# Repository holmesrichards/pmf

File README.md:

# Pole mixing filter

This is a multimode VCF in Kosmo format based on a [design](https://electricdruid.net/multimode-filters-part-2-pole-mixing-filters) by Electric Druid (ED). It uses pole mixing to achieve multiple filter behaviors.

## Design notes

### Changes from ED design

* 82k resistors (RF) changed to 100k; 91k resistors (RC) to fixed + trimmer.
* Added AC coupling capacitor on input signal to resonance compensation mixer.
* Added resistor on resonance input pin missing from original schematics. Changed its value from 51k to 120k.
* Added op amp buffers and pulldown resistors on LP1–4 after AC coupling capacitors.
* Added second inverting stage on input. Reduced first stage gain to 0.51 and increased output stage gain by the same factor.
* Changed ordering of 1st to 6th mixes.
* In 4P HP mix, changed 4.99k resistor to sum of 2k and 3k.
* Changed BP resistors for unity gain at peak.
* Changed 7th mix to {1, 2, 2, 0, 0} notch.
* Original had incorrect resistances for 8th mix; fixed.
* 7th and 8th mix have enough resistor footprints to implement any desired mix.
* Multiplexer replaced with rotary switch.
* Added header for expansion.

### Discussion

As discussed [here](Docs/tolerances.md), it is important that filter stages have unity DC gain and mixer ratios be correct at a level of about 1% or better, preferably more like 0.1% for the mixer resistors.

The 82k feedback resistors used in the ED design are a puzzle: Per the CEM3320 datasheet, they result in a gain of around 0.82. In the datasheet circuit these resistors are 100k giving gain 0.999. On the breadboard I found some gain variation (even if I matched the resistors), so I replaced the 91k resistors (RI, RC) with fixed + trimmer combinations.

If there is a DC offset on the input signal (if for instance it goes 0 to 5 V), then, due to its being DC coupled to the resonance compensation mixer, turning up the resonance CV would drive the DC offset of the output signal higher. Even with a 0 to 2 V input, the output could exceed 9 V due to the large offset. This is too large: With Vcc = 12 V, maximum output before clipping is about 9 V. Adding a capacitor to AC couple the input signal to the compensation mixer eliminates this problem.

The ED schematics omit a resistor on the resonance input pin. In the comments Tom Wiltshire says this should be 51k. I found this value would cause self oscillation to start up at a very low position of the resonance knob, so changed it to 120k.

With an input of 5 V (or -5 V) or above, the filter stage outputs would try to go to or above about 10 V. I reduced the input gain by a factor of 0.51 to keep below that limit. ±5 V is the standard audio signal range in my synth. Of course if you use two summed inputs they might exceed 5 V, so some additional attenuation may be needed. I also added a second inverting stage with the thought of preserving the phase going into the filter. However there is an inverting stage at the output, so it probably would have been better to leave this second stage out. Not quite sure what I was thinking!

ED's mixers have been re-ordered, just because I felt 2 pole should go before 4 pole. The E96 4.99k resistor has been replaced by E24 2k and 3k in series, because who want to order one resistor from DigiKey that Tayda doesn't carry? The resistor values used by ED in the BP mixers result in peak amplitudes 6 or 12 dB below the input level; I reduced them to get unity gain at the peaks. I wasn't that enthusiastic about the seventh filter — a rather weird combination of things giving rise to a sort of band pass plus notch response — so I replaced it with a second (sharper, deadlier) notch filter.

I didn't see much point in messing around with a multiplexer chip. I used a rotary switch instead. If you really want electronically selectable filter shapes, see the Expansion section below.

The mixers that are not selected by the rotary switch had floating outputs and corrupted the LP1–LP4 signals until I added op amp buffers after the AC coupling capacitors. I believe the same problem would occur with a multiplexer. To avoid bias current charging of the capacitors, I also added 1M resistors to ground between the capacitors and the op amps.

### Choose your own

To accommodate other builders with other preferences (or future me with other preferences), in the last two filters enough resistor (or jumper) footprints have been provided to build almost any mixer allowing whatever filter responses you want. Each of the LP1, LP2, LP3, and LP4 signals has two footprints in series. For example, to re-create ED's seventh filter, [0, 1, 3, 6, 4]: Omit the R<sub>IN</sub> resistor, use 30k and a wire jumper for the two R<sub>LP1</sub> resistors, 10k+jumper for R<sub>LP2</sub>, 2k+3K for R<sub>LP3</sub>, and 7.5k+jumper for R<sub>LP4</sub>. To build the filters shown in the schematic, follow the silkscreen: Use wire jumpers for the jumper footprints and leave the DNF footprints empty.

A catalog of 40+ filters is in [Docs/catalog.md](Docs/catalog.md).

### Expansion

There is an expansion header on the PCB. This could be used to mount a daughterboard giving more mixes. Or it could be used for a ribbon cable connection to an expansion module, which could e.g. provide user-changeable mixes (5 rotary switches?) or a microcontroller-based variable mixer, potentially even with CV input to switch mixes. This repo includes a design for a daughterboard providing four additional builder-defined mixes. As with filters 7 and 8 on the main module, there are two footprints for each of the LP1, LP2, LP3, and LP4 signals and you can populate both with resistors, use one resistor and one jumper, or omit both to get the mixes you desire. This daughterboard has not been built or tested yet.

### Filters

The filters are as follows. Numbers indicate coefficients for input, -LP1, LP2, -LP3, and LP4 mixing.

* 0, 0, 1, 0, 0 — 2 pole low pass
* 0, 0, 0, 0, 1 — 4 pole low pass
* 1, 2, 1, 0, 0 — 2 pole high pass
* 1, 4, 6, 4, 1 — 4 pole high pass
* 0, 2, 2, 0, 0 — 2 pole band pass
* 0, 0, 4, 8, 4 — 4 pole band pass
* 1, 2, 2, 0, 0 — Notch A
* 1, 2, 2, 2, 2 — Notch B

Here are Bode plots for these filters:

### Cancellation and tolerances

See discussion [here](Docs/tolerances.md).

## Software

The plots above were produced with a Python script included in this repo's Software folder. For a usage example see plots.sh in that folder. Libraries matplotlib, numpy, sys, and re are required. 

For the formulas for pole mixing upon which these plots are based, see [https://expeditionelectronics.com/Diy/Polemixing/math](https://expeditionelectronics.com/Diy/Polemixing/math). I believe there are some errors: the formulas for the imaginary parts of the numerator and denominator should have the opposite sign.

## Current draw
? mA +12 V, ? mA -12 V

## Photos

## Documentation

* [Schematic](Docs/pmf_schematic.pdf)
* PCB layout: [front of board 1](Docs/Layout/pmf_B1/pmf_B1_front.svg), [back of board 1](Docs/Layout/pmf_B1/pmf_B1_back.svg), [front of board 2](Docs/Layout/pmf_B2/pmf_B2_front.svg), [back of board 2](Docs/Layout/pmf_B2/pmf_B2_back.svg)
* [BOM](Docs/BOM/pmf_bom.md)
* [Daughterboard schematic](Docs/pmf_daughter_schematic.pdf)
* Daughterboard PCB layout: [front](Docs/Layout/pmf_daughter/pmf_daughter_front.svg), [back](Docs/Layout/pmf_daughter/pmf_daughter_back.svg)
* [Daughterboard BOM](Docs/BOM/pmf_daughter_bom.md)
* [Blog post](https://analogoutputblog.wordpress.com/2023/05/04/pole-mixing-filter/)

## GitHub repository

* [https://github.com/holmesrichards/pmf](https://github.com/holmesrichards/pmf)

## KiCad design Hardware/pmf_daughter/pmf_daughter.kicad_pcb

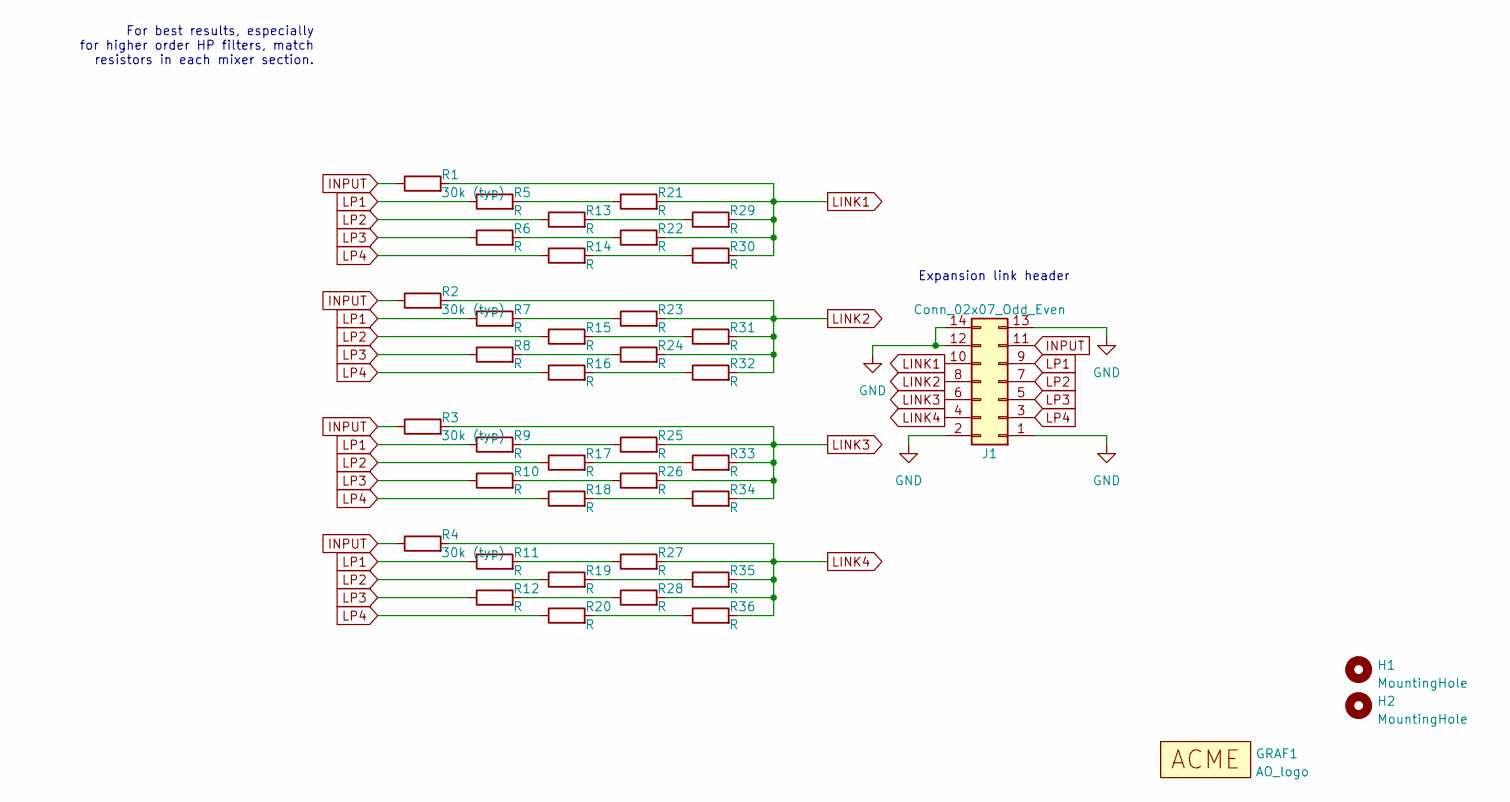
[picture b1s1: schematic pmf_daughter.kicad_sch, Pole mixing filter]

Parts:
GRAF1: AO_logo; analogoutput_12mm
H1, H2: MountingHole; MountingHole_3.2mm_M3
J1: Conn_02x07_Odd_Even; PinSocket_2x07_P2.54mm_Vertical
R1, R2, R3, R4: 30k (typ); R_Axial_DIN0207_L6.3mm_D2.5mm_P10.16mm_Horizontal
R5, R6, R7, R8, R9, R10, R11, R12, R13, R14, R15, R16, R17, R18, R19, R20, R21, R22, R23, R24, R25, R26, R27, R28, R29, R30, R31, R32, R33, R34, R35, R36: R; R_Axial_DIN0207_L6.3mm_D2.5mm_P10.16mm_Horizontal

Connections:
GND: J1.1, J1.2, J1.12, J1.13, J1.14
INPUT: J1.11, R1.1, R2.1, R3.1, R4.1
LINK1: J1.10, R1.2, R21.2, R22.2, R29.2, R30.2
LINK2: J1.8, R2.2, R23.2, R24.2, R31.2, R32.2
LINK3: J1.6, R3.2, R25.2, R26.2, R33.2, R34.2
LINK4: J1.4, R4.2, R27.2, R28.2, R35.2, R36.2
LP1: J1.9, R5.1, R7.1, R9.1, R11.1
LP2: J1.7, R13.1, R15.1, R17.1, R19.1
LP3: J1.5, R6.1, R8.1, R10.1, R12.1
LP4: J1.3, R14.1, R16.1, R18.1, R20.1
unnamed: R10.2, R26.1
unnamed: R11.2, R27.1
unnamed: R12.2, R28.1
unnamed: R13.2, R29.1
unnamed: R14.2, R30.1
unnamed: R15.2, R31.1
unnamed: R16.2, R32.1
unnamed: R17.2, R33.1
unnamed: R18.2, R34.1
unnamed: R19.2, R35.1
unnamed: R20.2, R36.1
unnamed: R5.2, R21.1
unnamed: R6.2, R22.1
unnamed: R7.2, R23.1
unnamed: R8.2, R24.1
unnamed: R9.2, R25.1

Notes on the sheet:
Expansion link header
For best results, especially for higher order HP filters, match resistors in each mixer section.

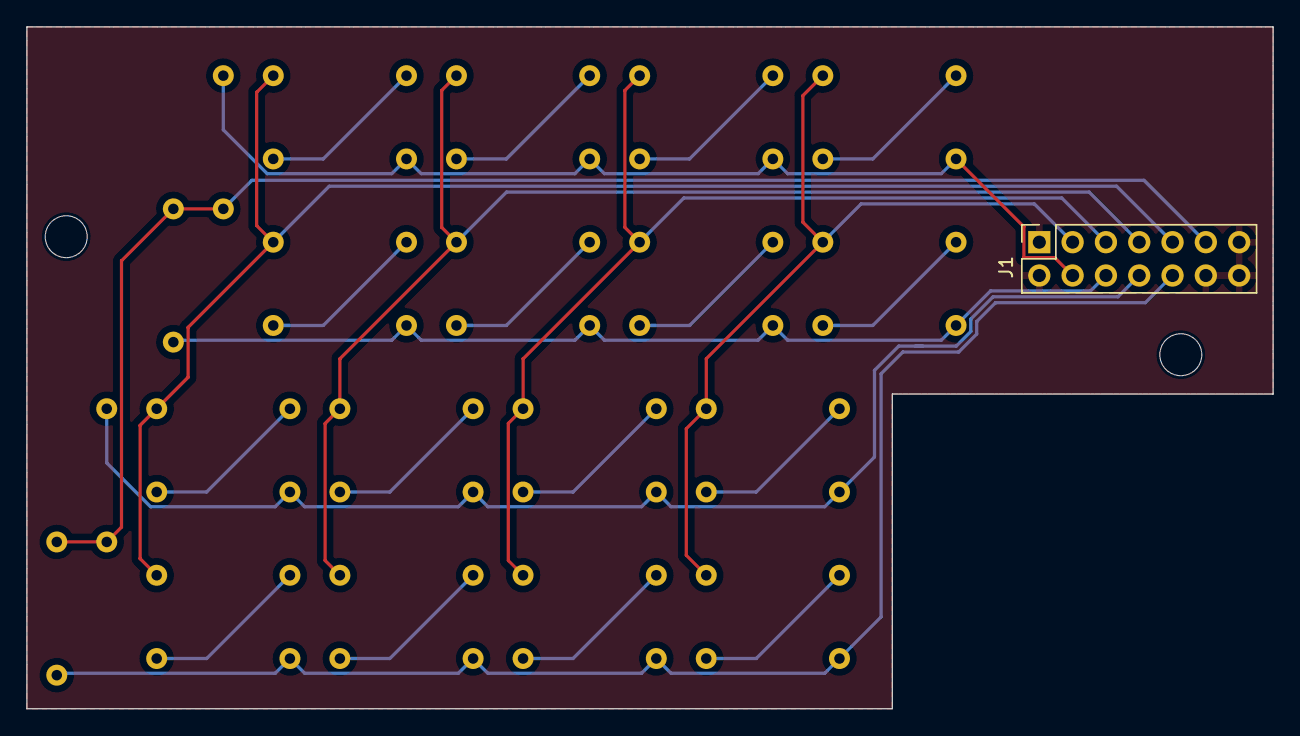
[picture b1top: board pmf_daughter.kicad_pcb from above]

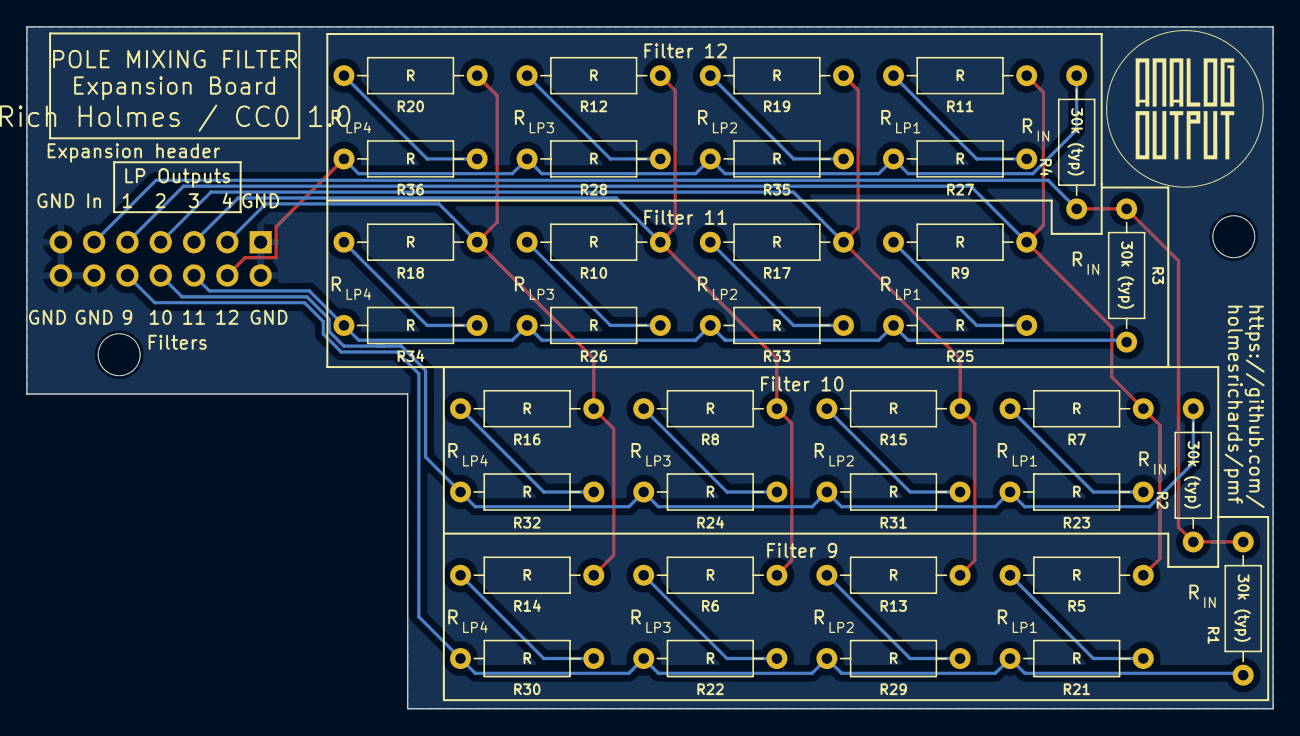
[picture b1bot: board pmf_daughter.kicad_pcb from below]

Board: 2 copper layers, 95.0 x 52.0 mm, 40 parts (37 on the bottom side), 26 nets.

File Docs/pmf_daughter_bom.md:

# pmf_daughter.kicad_sch BOM

Mon 16 Jan 2023 01:00:04 PM EST

Generated from schematic by Eeschema 7.0.0-rc1-unknown-00d77f624a~164~ubuntu22.04.1

**Component Count:** 37

| Refs | Qty | Component | Description | Vendor |
| ----- | --- | ---- | ----------- | ---- |
| J1 | 1 | Conn_02x07_Odd_Even | Generic connector, double row, 02x07, odd/even pin numbering scheme (row 1 odd numbers, row 2 even numbers), script generated (kicad-library-utils/schlib/autogen/connector/) |  |
| R1, R2, R3, R4 | 4 | 30k (typ) | Resistor | Tayda |
| R5, R6, R7, R8, R9, R10, R11, R12, R13, R14, R15, R16, R17, R18, R19, R20, R21, R22, R23, R24, R25, R26, R27, R28, R29, R30, R31, R32, R33, R34, R35, R36 | 32 | R | Resistor | Tayda |

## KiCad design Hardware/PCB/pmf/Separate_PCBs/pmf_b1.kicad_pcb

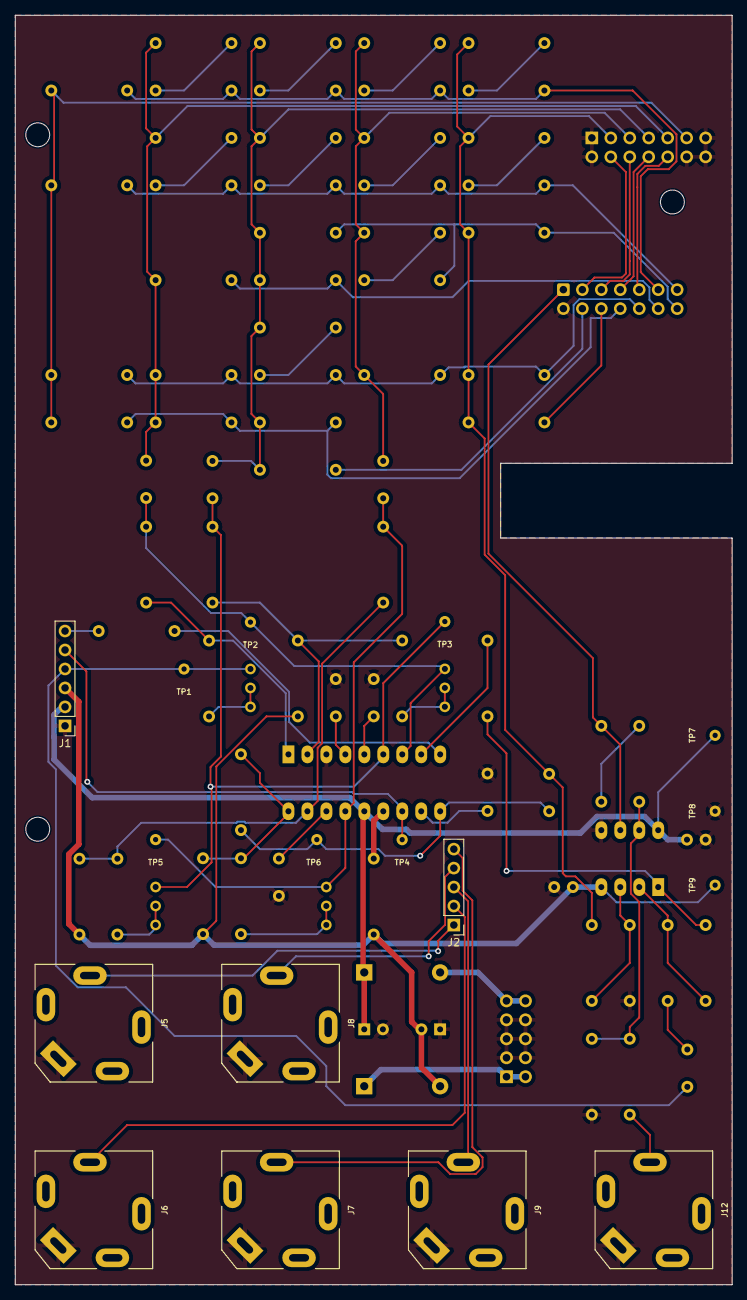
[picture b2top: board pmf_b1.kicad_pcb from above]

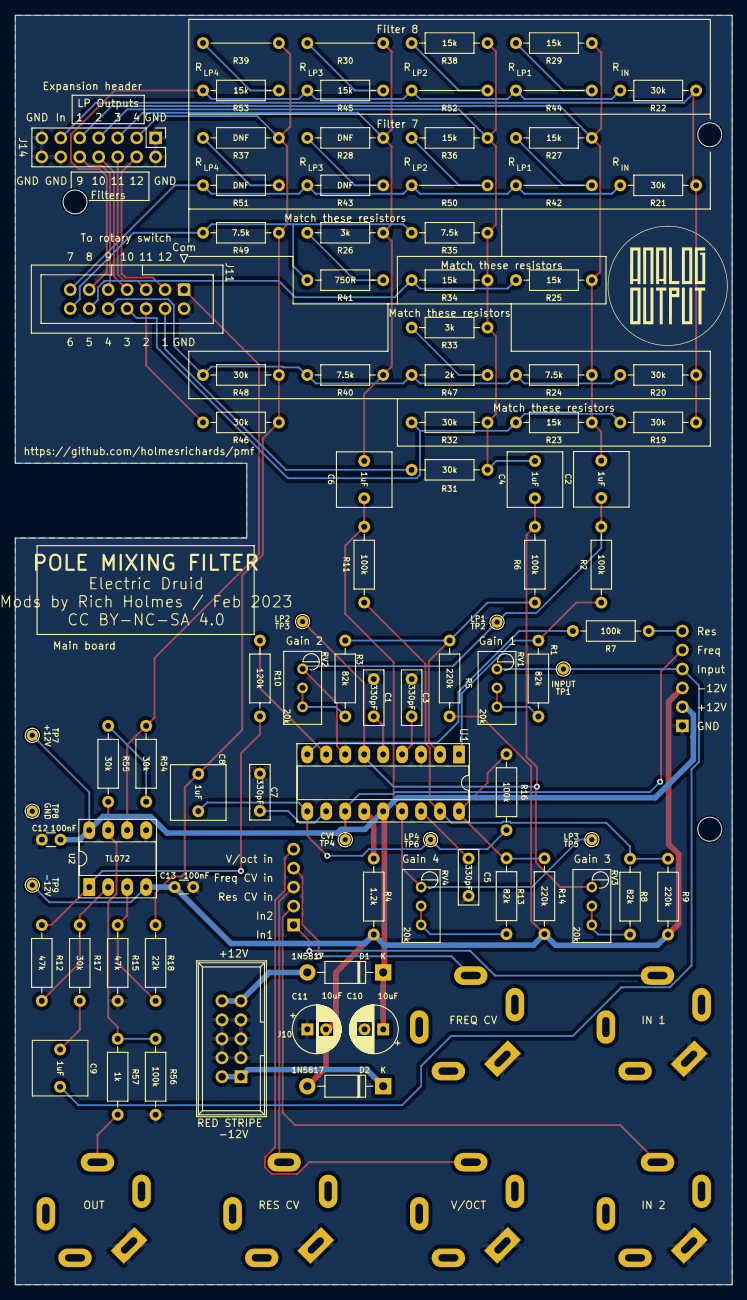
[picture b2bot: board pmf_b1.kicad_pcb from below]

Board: 2 copper layers, 96.0 x 170.0 mm, 104 parts (91 on the bottom side), 67 nets.

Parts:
B1: Board; Board_Marker
C1, C3, C5, C7: 330pF; C_Rect_L7.2mm_W2.5mm_P5.00mm_FKS2_FKP2_MKS2_MKP2
C2, C4, C6, C8, C9: 1uF; C_Rect_L7.2mm_W7.2mm_P5.00mm_FKS2_FKP2_MKS2_MKP2
C10, C11: 10uF; CP_Radial_D6.3mm_P2.50mm
C12, C13: 100nF; C_Disc_D3.0mm_W1.6mm_P2.50mm
D1, D2: 1N5817; D_DO-41_SOD81_P10.16mm_Horizontal
GRAF1: Holes; pmf_panel_holes
GRAF3: AO_logo; analogoutput
H1, H2, H3: MountingHole; MountingHole_3.2mm_M3
J1: Conn_01x06_Pin; PinHeader_1x06_P2.54mm_Vertical
J2: Conn_01x05_Pin; PinHeader_1x05_P2.54mm_Vertical
J5, J6, J7, J8, J9, J12: AudioJack2; Jack_6.35mm_PJ_629HAN_slots
J10: Synth_power_2x5; Power_Header
J11: Conn_02x07_Odd_Even; IDC-Header_2x07_P2.54mm_Vertical
J14: Conn_02x07_Odd_Even; PinHeader_2x07_P2.54mm_Vertical
R1, R3, R8, R13: 82k; R_Axial_DIN0207_L6.3mm_D2.5mm_P10.16mm_Horizontal
R2, R6, R7, R11, R16, R56: 100k; R_Axial_DIN0207_L6.3mm_D2.5mm_P10.16mm_Horizontal
R4: 1.2k; R_Axial_DIN0207_L6.3mm_D2.5mm_P10.16mm_Horizontal
R5, R9, R14: 220k; R_Axial_DIN0207_L6.3mm_D2.5mm_P10.16mm_Horizontal
R10: 120k; R_Axial_DIN0207_L6.3mm_D2.5mm_P10.16mm_Horizontal
R12, R15: 47k; R_Axial_DIN0207_L6.3mm_D2.5mm_P10.16mm_Horizontal
R17, R19, R20, R21, R22, R31, R32, R46, R48, R54, R55: 30k; R_Axial_DIN0207_L6.3mm_D2.5mm_P10.16mm_Horizontal
R18: 22k; R_Axial_DIN0207_L6.3mm_D2.5mm_P10.16mm_Horizontal
R23, R25, R27, R29, R34, R36, R38, R45, R53: 15k; R_Axial_DIN0207_L6.3mm_D2.5mm_P10.16mm_Horizontal
R24, R35, R40, R49: 7.5k; R_Axial_DIN0207_L6.3mm_D2.5mm_P10.16mm_Horizontal
R26, R33: 3k; R_Axial_DIN0207_L6.3mm_D2.5mm_P10.16mm_Horizontal
R28, R37, R43, R51: DNF; R_Axial_DNF_L6.3mm_P10.16mm_Horizontal
R30, R39, R42, R44, R50, R52: 0R; Wire_Jumper_10.16
R41: 750R; R_Axial_DIN0207_L6.3mm_D2.5mm_P10.16mm_Horizontal
R47: 2k; R_Axial_DIN0207_L6.3mm_D2.5mm_P10.16mm_Horizontal
R57: 1k; R_Axial_DIN0207_L6.3mm_D2.5mm_P10.16mm_Horizontal
RV1, RV2, RV3, RV4: 20k; Potentiometer_Bourns_3296W_Vertical_standard
TP1: INPUT; TestPoint_THTPad_D1.5mm_Drill0.7mm
TP2: LP1; TestPoint_THTPad_D1.5mm_Drill0.7mm
TP3: LP2; TestPoint_THTPad_D1.5mm_Drill0.7mm
TP4: CVf; TestPoint_THTPad_D1.5mm_Drill0.7mm
TP5: LP3; TestPoint_THTPad_D1.5mm_Drill0.7mm
TP6: LP4; TestPoint_THTPad_D1.5mm_Drill0.7mm
TP7: +12V; TestPoint_THTPad_D1.5mm_Drill0.7mm
TP8: GND; TestPoint_THTPad_D1.5mm_Drill0.7mm
TP9: -12V; TestPoint_THTPad_D1.5mm_Drill0.7mm
U1: AS3320; DIP-18_W7.62mm_Socket_LongPads
U2: TL072; DIP-8_W7.62mm_Socket_LongPads

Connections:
Board_0-+12V: C10.1, C12.1, D1.1 (K), J1.2, TP7.1, U1.14 (VCC), U2.8 (V+)
Board_0--12V: C11.2, C13.2, D2.2 (A), J1.3, R4.1, R5.2, R9.2, R14.2, TP9.1, U2.4 (V-)
Board_0-/Filter core/FREQ_CV: J1.5, TP4.1, U1.12 (VCFI)
Board_0-/Filter core/INPUT: C9.2, J1.4, RV1.1, TP1.1
Board_0-/Filter core/RES_CV: J1.6, R7.1
Board_0-/Other stuff/+12V_IN: D1.2 (A), J10.9 (+12V), J10.10 (+12V)
Board_0-/Other stuff/-12V_IN: D2.1 (K), J10.1 (-12V), J10.2 (-12V)
Board_0-/Other stuff/FREQ_CV_IN: J2.4, J8.T
Board_0-/Other stuff/IN1: J2.1, J5.T
Board_0-/Other stuff/IN2: J2.2, J6.T
Board_0-/Other stuff/M_BP2: J11.12, R25.2, R34.2
Board_0-/Other stuff/M_BP4: J11.14, R35.2, R41.2, R49.2
Board_0-/Other stuff/M_HP2: J11.8, R19.2, R23.2, R32.2
Board_0-/Other stuff/M_HP4: J11.10, R20.2, R24.2, R40.2, R47.2, R48.2
Board_0-/Other stuff/M_LP2: J11.4, R31.2
Board_0-/Other stuff/M_LP4: J11.6, R46.2
Board_0-/Other stuff/M_NTA: J11.13, R21.2, R42.2, R43.2, R50.2, R51.2
Board_0-/Other stuff/M_NTB: J11.11, R22.2, R44.2, R45.2, R52.2, R53.2
Board_0-/Other stuff/OUT: J12.T, R57.2
Board_0-/Other stuff/RES_CV_IN: J2.3, J9.T
Board_0-/Other stuff/V/OCT_IN: J2.5, J7.T
Board_0-GND: C1.2, C3.2, C5.2, C7.2, C10.2, C11.1, C12.2, C13.1, J1.1, J5.S, J6.S, J7.S, J8.S, J9.S, J10.3 (GND), J10.4 (GND), J10.5 (GND), J10.6 (GND), J10.7 (GND), J10.8 (GND), J11.2, J12.S, J14.1, J14.2, J14.12, J14.13, J14.14, R15.2, R56.2, TP8.1, U1.3 (GND), U2.5 (+)
Board_0-INPUT: J14.11, R19.1, R20.1, R21.1, R22.1
Board_0-LINK1: J11.9, J14.10
Board_0-LINK2: J11.7, J14.8
Board_0-LINK3: J11.5, J14.6
Board_0-LINK4: J11.3, J14.4
Board_0-LP1: C2.2, J14.9, R23.1, R24.1, R25.1, R27.1, R29.1
Board_0-LP2: C4.2, J14.7, R31.1, R32.1, R33.1, R34.1, R35.1, R36.1, R38.1
Board_0-LP3: C6.2, J14.5, R26.1, R28.1, R30.1, R40.1
Board_0-LP4: C8.2, J14.3, R18.2, R37.1, R39.1, R46.1, R48.1, R49.1
Board_0-Net-(C9-Pad1): C9.1, R17.2
Board_0-Net-(J11-Pin_1): J11.1, R54.1, U2.6 (-)
Board_0-Net-(R1-Pad1): R1.1, RV1.2, RV1.3
Board_0-Net-(R3-Pad1): R3.1, RV2.2, RV2.3
Board_0-Net-(R8-Pad1): R8.1, RV3.2, RV3.3
Board_0-Net-(R10-Pad2): R10.2, R12.1, U2.1
Board_0-Net-(R13-Pad1): R13.1, RV4.2, RV4.3
Board_0-Net-(R26-Pad2): R26.2, R41.1
Board_0-Net-(R27-Pad2): R27.2, R42.1
Board_0-Net-(R28-Pad2): R28.2, R43.1
Board_0-Net-(R29-Pad2): R29.2, R44.1
Board_0-Net-(R30-Pad2): R30.2, R45.1
Board_0-Net-(R33-Pad2): R33.2, R47.1
Board_0-Net-(R36-Pad2): R36.2, R50.1
Board_0-Net-(R37-Pad2): R37.2, R51.1
Board_0-Net-(R38-Pad2): R38.2, R52.1
Board_0-Net-(R39-Pad2): R39.2, R53.1
Board_0-Net-(R54-Pad2): R54.2, R55.1
Board_0-Net-(R55-Pad2): R55.2, R56.1, R57.1, U2.7
Board_0-Net-(U1-CAP1): C1.1, U1.5 (CAP1)
Board_0-Net-(U1-CAP2): C3.1, U1.4 (CAP2)
Board_0-Net-(U1-CAP3): C5.1, U1.16 (CAP3)
Board_0-Net-(U1-CAP4): C7.1, U1.11 (CAP4)
Board_0-Net-(U1-IN1): R1.2, R2.1, U1.1 (IN1)
Board_0-Net-(U1-IN2): R3.2, R5.1, R6.1, U1.2 (IN2)
Board_0-Net-(U1-IN3): R8.2, R9.1, R11.1, U1.17 (IN3)
Board_0-Net-(U1-IN4): R13.2, R14.1, R16.1, U1.18 (IN4)
Board_0-Net-(U1-IRES): R7.2, U1.9 (IRES)
Board_0-Net-(U1-OUT1): C2.1, R2.2, RV2.1, TP2.1, U1.7 (OUT1)
Board_0-Net-(U1-OUT2): C4.1, R6.2, RV3.1, TP3.1, U1.6 (OUT2)
Board_0-Net-(U1-OUT3): C6.1, R11.2, RV4.1, TP5.1, U1.15 (OUT3)
Board_0-Net-(U1-OUT4): C8.1, R16.2, TP6.1, U1.10 (OUT4)
Board_0-Net-(U1-VEE): R4.2, U1.13 (VEE)
Board_0-Net-(U1-VRES): R10.1, U1.8 (VRES)
Board_0-Net-(U2A-+): R15.1, R18.1, U2.3 (+)
Board_0-Net-(U2A--): R12.2, R17.1, U2.2 (-)

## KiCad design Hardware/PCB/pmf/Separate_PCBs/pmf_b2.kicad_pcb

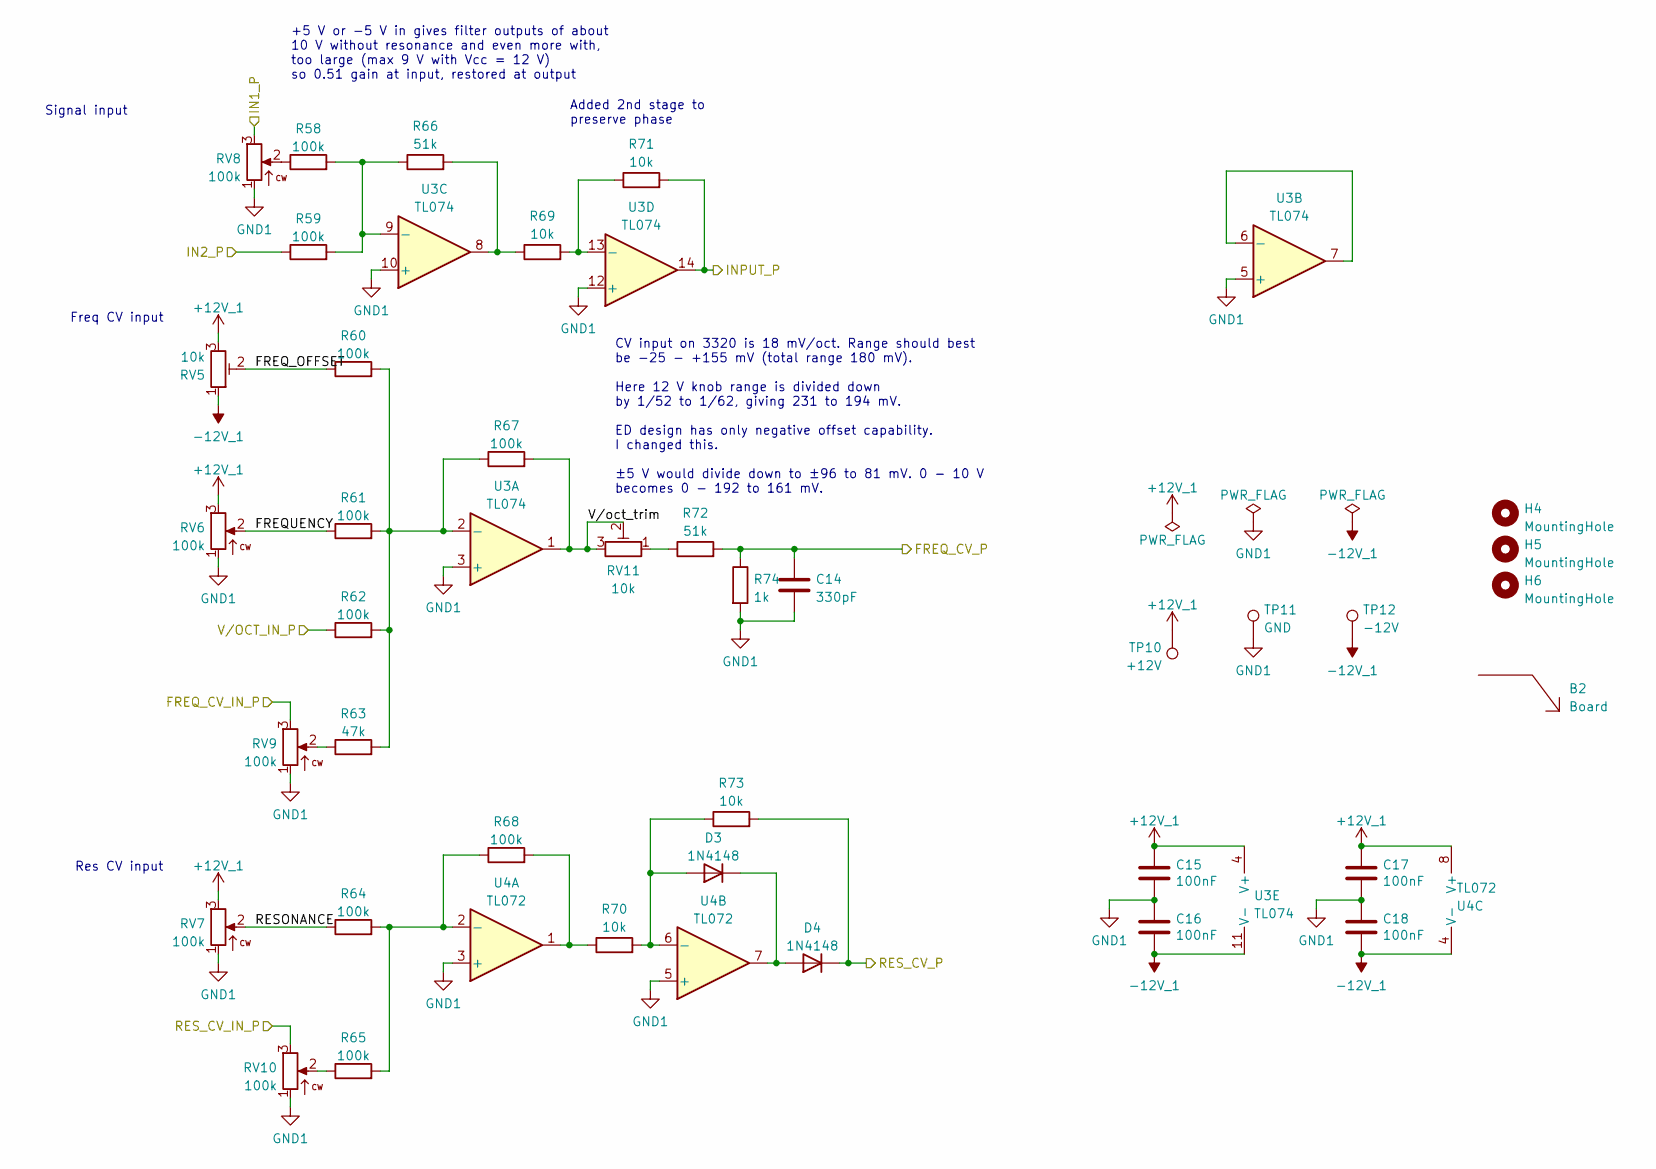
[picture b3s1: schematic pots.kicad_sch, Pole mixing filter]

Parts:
B2: Board; Board_Marker
C14: 330pF; C_Rect_L7.2mm_W2.5mm_P5.00mm_FKS2_FKP2_MKS2_MKP2; Part FKP2D003301D00JSSD
C15, C16, C17, C18: 100nF; C_Disc_D3.0mm_W1.6mm_P2.50mm
D3, D4: 1N4148; D_DO-35_SOD27_P7.62mm_Horizontal
H4, H5, H6: MountingHole; MountingHole_3.2mm_M3
R58, R59, R60, R61, R62, R64, R65, R67, R68: 100k; R_Axial_DIN0207_L6.3mm_D2.5mm_P10.16mm_Horizontal
R63: 47k; R_Axial_DIN0207_L6.3mm_D2.5mm_P10.16mm_Horizontal
R66, R72: 51k; R_Axial_DIN0207_L6.3mm_D2.5mm_P10.16mm_Horizontal
R69, R70, R71, R73: 10k; R_Axial_DIN0207_L6.3mm_D2.5mm_P10.16mm_Horizontal
R74: 1k; R_Axial_DIN0207_L6.3mm_D2.5mm_P10.16mm_Horizontal
RV5, RV11: 10k; Potentiometer_Bourns_3296X_Horizontal
RV6, RV7, RV8, RV9, RV10: 100k; Potentiometer_Alpha_16mm_Single_Vertical
TP10: +12V; TestPoint_THTPad_D1.5mm_Drill0.7mm
TP11: GND; TestPoint_THTPad_D1.5mm_Drill0.7mm
TP12: -12V; TestPoint_THTPad_D1.5mm_Drill0.7mm
U3: TL074; DIP-14_W7.62mm_Socket_LongPads
U4: TL072; DIP-8_W7.62mm_Socket_LongPads

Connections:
Board_0-+12V_1: C15.1, C17.1, RV5.3, RV6.3, RV7.3, TP10.1, U3.4 (V+), U4.8 (V+); also elsewhere on the board
Board_0--12V_1: C16.2, C18.2, RV5.1, TP12.1, U3.11 (V-), U4.4 (V-); also elsewhere on the board
Board_0-/Pots board/FREQUENCY: R61.1, RV6.2
Board_0-/Pots board/FREQ_CV_IN_P: RV9.3; also elsewhere on the board
Board_0-/Pots board/FREQ_CV_P: C14.1, R72.2, R74.1; also elsewhere on the board
Board_0-/Pots board/FREQ_OFFSET: R60.1, RV5.2
Board_0-/Pots board/IN1_P: RV8.3; also elsewhere on the board
Board_0-/Pots board/IN2_P: R59.1; also elsewhere on the board
Board_0-/Pots board/INPUT_P: R71.2, U3.14; also elsewhere on the board
Board_0-/Pots board/RESONANCE: R64.1, RV7.2
Board_0-/Pots board/RES_CV_IN_P: RV10.3; also elsewhere on the board
Board_0-/Pots board/RES_CV_P: D4.1 (K), R73.2; also elsewhere on the board
Board_0-/Pots board/V/OCT_IN_P: R62.1; also elsewhere on the board
Board_0-/Pots board/V/oct_trim: R67.2, RV11.2, RV11.3, U3.1
Board_0-GND1: C14.2, C15.2, C16.1, C17.2, C18.1, R74.2, RV6.1, RV7.1, RV8.1, RV9.1, RV10.1, TP11.1, U3.3 (+), U3.5 (+), U3.10 (+), U3.12 (+), U4.3 (+), U4.5 (+); also elsewhere on the board
Board_0-Net-(D3-A): D3.2 (A), R70.2, R73.1, U4.6 (-)
Board_0-Net-(D3-K): D3.1 (K), D4.2 (A), U4.7
Board_0-Net-(R58-Pad1): R58.1, RV8.2
Board_0-Net-(R63-Pad1): R63.1, RV9.2
Board_0-Net-(R65-Pad1): R65.1, RV10.2
Board_0-Net-(R66-Pad2): R66.2, R69.1, U3.8
Board_0-Net-(R68-Pad2): R68.2, R70.1, U4.1
Board_0-Net-(R72-Pad1): R72.1, RV11.1
Board_0-Net-(U3A--): R60.2, R61.2, R62.2, R63.2, R67.1, U3.2 (-)
Board_0-Net-(U3B--): U3.6 (-), U3.7
Board_0-Net-(U3C--): R58.2, R59.2, R66.1, U3.9 (-)
Board_0-Net-(U3D--): R69.2, R71.1, U3.13 (-)
Board_0-Net-(U4A--): R64.2, R65.2, R68.1, U4.2 (-)

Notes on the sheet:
Added 2nd stage to preserve phase
CV input on 3320 is 18 mV/oct. Range should best be -25 - +155 mV (total range 180 mV). Here 12 V knob range is divided down by 1/52 to 1/62, giving 231 to 194 mV. ED design has only negative offset capability. I changed this. ±5 V would divide down to ±96 to 81 mV. 0 - 10 V becomes 0 - 192 to 161 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
+5 V or -5 V in gives filter outputs of about 10 V without resonance and even more with, too large (max 9 V with Vcc = 12 V) so 0.51 gain at input, restored at output
Signal input
Freq CV input
Res CV input

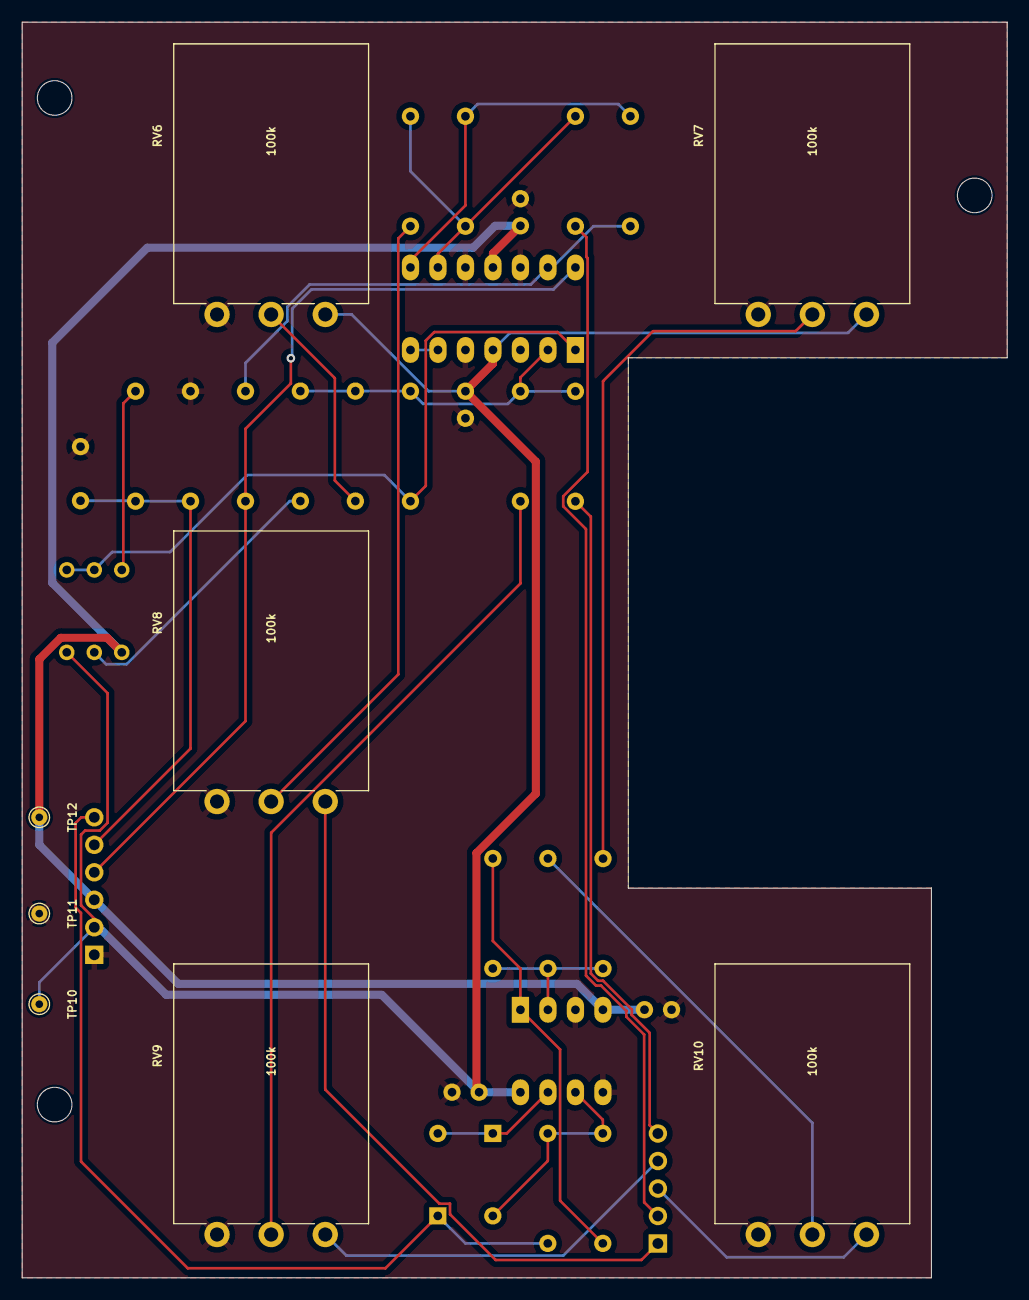
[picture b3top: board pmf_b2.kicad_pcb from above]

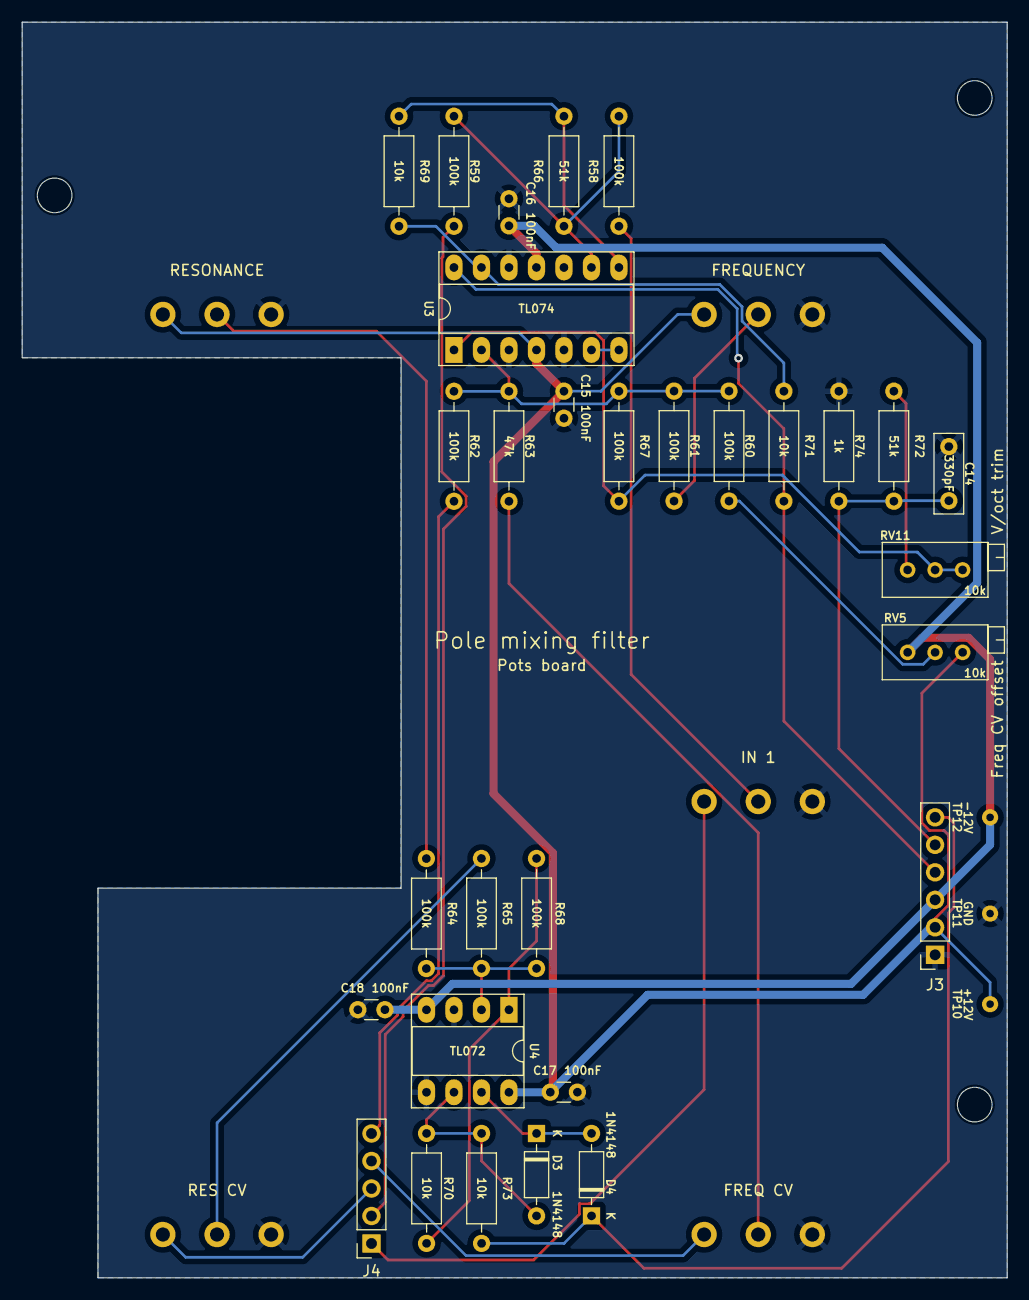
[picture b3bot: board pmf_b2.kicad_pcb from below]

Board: 2 copper layers, 91.0 x 116.0 mm, 43 parts (30 on the bottom side), 28 nets.

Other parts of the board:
GRAF2: Holes; pmf_panel_holes
J3: Conn_01x06_Socket; PinSocket_1x06_P2.54mm_Vertical
J4: Conn_01x05_Socket; PinSocket_1x05_P2.54mm_Vertical

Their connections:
Board_0-+12V_1: J3.2; also elsewhere on the board
Board_0--12V_1: J3.3; also elsewhere on the board
Board_0-/Pots board/FREQ_CV_IN_P: J4.4; also elsewhere on the board
Board_0-/Pots board/FREQ_CV_P: J3.5; also elsewhere on the board
Board_0-/Pots board/IN1_P: J4.1; also elsewhere on the board
Board_0-/Pots board/IN2_P: J4.2; also elsewhere on the board
Board_0-/Pots board/INPUT_P: J3.4; also elsewhere on the board
Board_0-/Pots board/RES_CV_IN_P: J4.3; also elsewhere on the board
Board_0-/Pots board/RES_CV_P: J3.6; also elsewhere on the board
Board_0-/Pots board/V/OCT_IN_P: J4.5; also elsewhere on the board
Board_0-GND1: J3.1; also elsewhere on the board

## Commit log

2023-01-16 Initial version
2023-01-17 Font change; GND instead of NC on d-board
2023-01-17 Don't require comma
2023-01-18 Improvements to polemix.py; example shell script; split off tolerances discussion to new md file
2023-01-18 Add more plots to plots.sh
2023-01-18 Label correction
2023-01-19 Re-invert input
2023-01-19 Reorganize filter core schematic
2023-01-19 Resistor matching labels
2023-01-19 Catalog; figure sizes
2023-01-19 Rename libraries
2023-01-19 Larger resistor for resonance input
2023-01-20 Removed R_EE trimmer
2023-01-20 Add missing resistor
2023-01-20 Reposition pot board trimmers; ±12 V range for CV offset
2023-01-20 Update docs
2023-01-21 Remove VRES bias
2023-01-22 Reduce amplitude at input and restore at output
2023-01-23 README and tolerances doc updates
2023-01-24 Lower gain at input and higher at output; better justification for AC coupling at compensation mixer
2023-01-24 README and tolerances.md improvements
2023-01-25 Large attenuation and amplification
2023-01-25 Gain variation even with matched resistors
2023-01-25 CVf test point; disambiguate heirarchical symbols
2023-01-25 Update documents
2023-01-25 Bigger trimmers for RC; slightly move expansion header
2023-01-26 Hardware symbols test
2023-01-29 Return to smaller trimmer values; make core schematic clearer; restore munged footprints
2023-01-29 rm unintended files
2023-01-29 ignored files
2023-01-29 Correct README
2023-02-05 Libraries to folder
2023-02-05 README update for libraries
2023-02-12 Pre fab tweaks, Gerbers, BOM
2023-02-13 Text boxes
2023-02-14 Knobs, new hardware refs, improved BOM format
2023-02-22 rm libraries
2023-02-22 Libraries in new place
2023-03-08 rm submodules
2023-03-09 Docs
2023-03-11 rm omit from BOM and board
2023-03-11 Separate 2D directories for k-projects
2023-03-12 reduce heirarchy; docs
2023-03-31 Panel
2023-03-31 Calibration doc
2023-03-31 Global labels to heir, fixing input bug; buffer LP1-4; more clearance for rot switch
2023-04-04 Docs; add bias current resistors
2023-05-03 PCB updates; docs
2023-05-03 LICENSE
2023-05-04 It's Kosmo
2023-05-04 Correct docs links
2023-05-05 Second stage on input is probably counterproductive
2023-05-05 Remove second input stage
2023-05-05 DIP14->DIP8
2023-05-05 Panel image
2023-05-06 Redo catalog images
2023-05-06 12 catalog pages
2023-05-08 README update
2023-05-18 Docs; rm Gerbers pending resolution of kikit problem
2023-05-18 Photos

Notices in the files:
Hardware/PCB/pmf/Separate_PCBs/pmf_b1.kicad_pcb:
CC BY-NC-SA 4.0
Hardware/pmf_daughter/pmf_daughter.kicad_pcb:
Rich Holmes / CC0 1.0
